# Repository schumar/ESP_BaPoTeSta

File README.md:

#  ESP8266 Battery Powered Temperature Station

## Moved to GitLab

This project has moved to [GitLab/schumar/ESP_BaPoTeSta](https://gitlab.com/schumar/ESP_BaPoTeSta)

## Intro

Using only an ESP8266 (no Atmel AVR) and a sensor, it's possible to build a very cheap and power-efficient WiFi-enabled weather station.

### Pictures of v0.3

### Pictures of v0.5

### Pictures of v0.6

### Maintenance Web-Interface

## Current state

I've already built 3 sensors of v0.3, and around 60 of v0.5.  
Right now I'm working on a major redesign of the board, and improving the firmware.

The sensors are reporting their data via MQTT, so the data can be received with [OpenHAB](http://www.openhab.org/),
[FHEM](http://fhem.de/fhem.html) or a small Perl script.

"Release early, release often" -- so don't expect to be able to clone this repo and have a working IoThingy 10 minutes later :)

## Screenshot

## Technical details

-> Read the source, stare at my KiCAD schematic :)

## BOM

Quick calculation: 1 board would cost ca. 4.81 to 7.50 USD (excl. batteries),
depending on which sensors you want. (Calculation for an order of 30 boards)

Part|Need/Board|URL|per piece|per board
----|---------:|---|----------:|----------:|
PCB|1|http://dev.dangerousprototypes.com/store/pcbs|0.50|0.50
PinHdr|11|http://www.aliexpress.com/item/x/32537378399.html|0.01|0.09
1uF 1206|2|http://www.aliexpress.com/store/1361740|0.03|0.06
10uF|1|http://www.aliexpress.com/item/x/32260294384.html|0.07|0.07
ESP8266|1|http://www.aliexpress.com/item/x/32519328481.html|1.93|1.93
10k 1206|10|http://www.aliexpress.com/item/x/32569352008.html|0.01|0.09
56k 1206|1|http://www.aliexpress.com/item/x/32567865953.html|0.02|0.02
MCP1700|1|http://www.aliexpress.com/item/x/32523953207.html|0.36|0.36
BatteryCase|1|http://www.aliexpress.com/item/x/2022527017.html|1.06|1.06
**Sub-Total**||||**4.18**
DS18B20|1|http://www.aliexpress.com/item/x/32576213069.html|0.63|0.63
DHT22|1|http://www.aliexpress.com/item/x/32544057083.html|2.70|2.70
**Only DS18B20**||||**4.81**
**Only DHT22**||||**6.87**
**Both**||||**7.50**

## To Do

see [Issues](https://gitlab.com/schumar/ESP_BaPoTeSta/issues)

## Thanks

* Many thanks to all the people working on the [Arduino core for ESP8266](https://github.com/esp8266/Arduino)
* Cheers to [jdunmire](https://github.com/jdunmire/kicad-ESP8266) for his ESP8266 KiCAD library!

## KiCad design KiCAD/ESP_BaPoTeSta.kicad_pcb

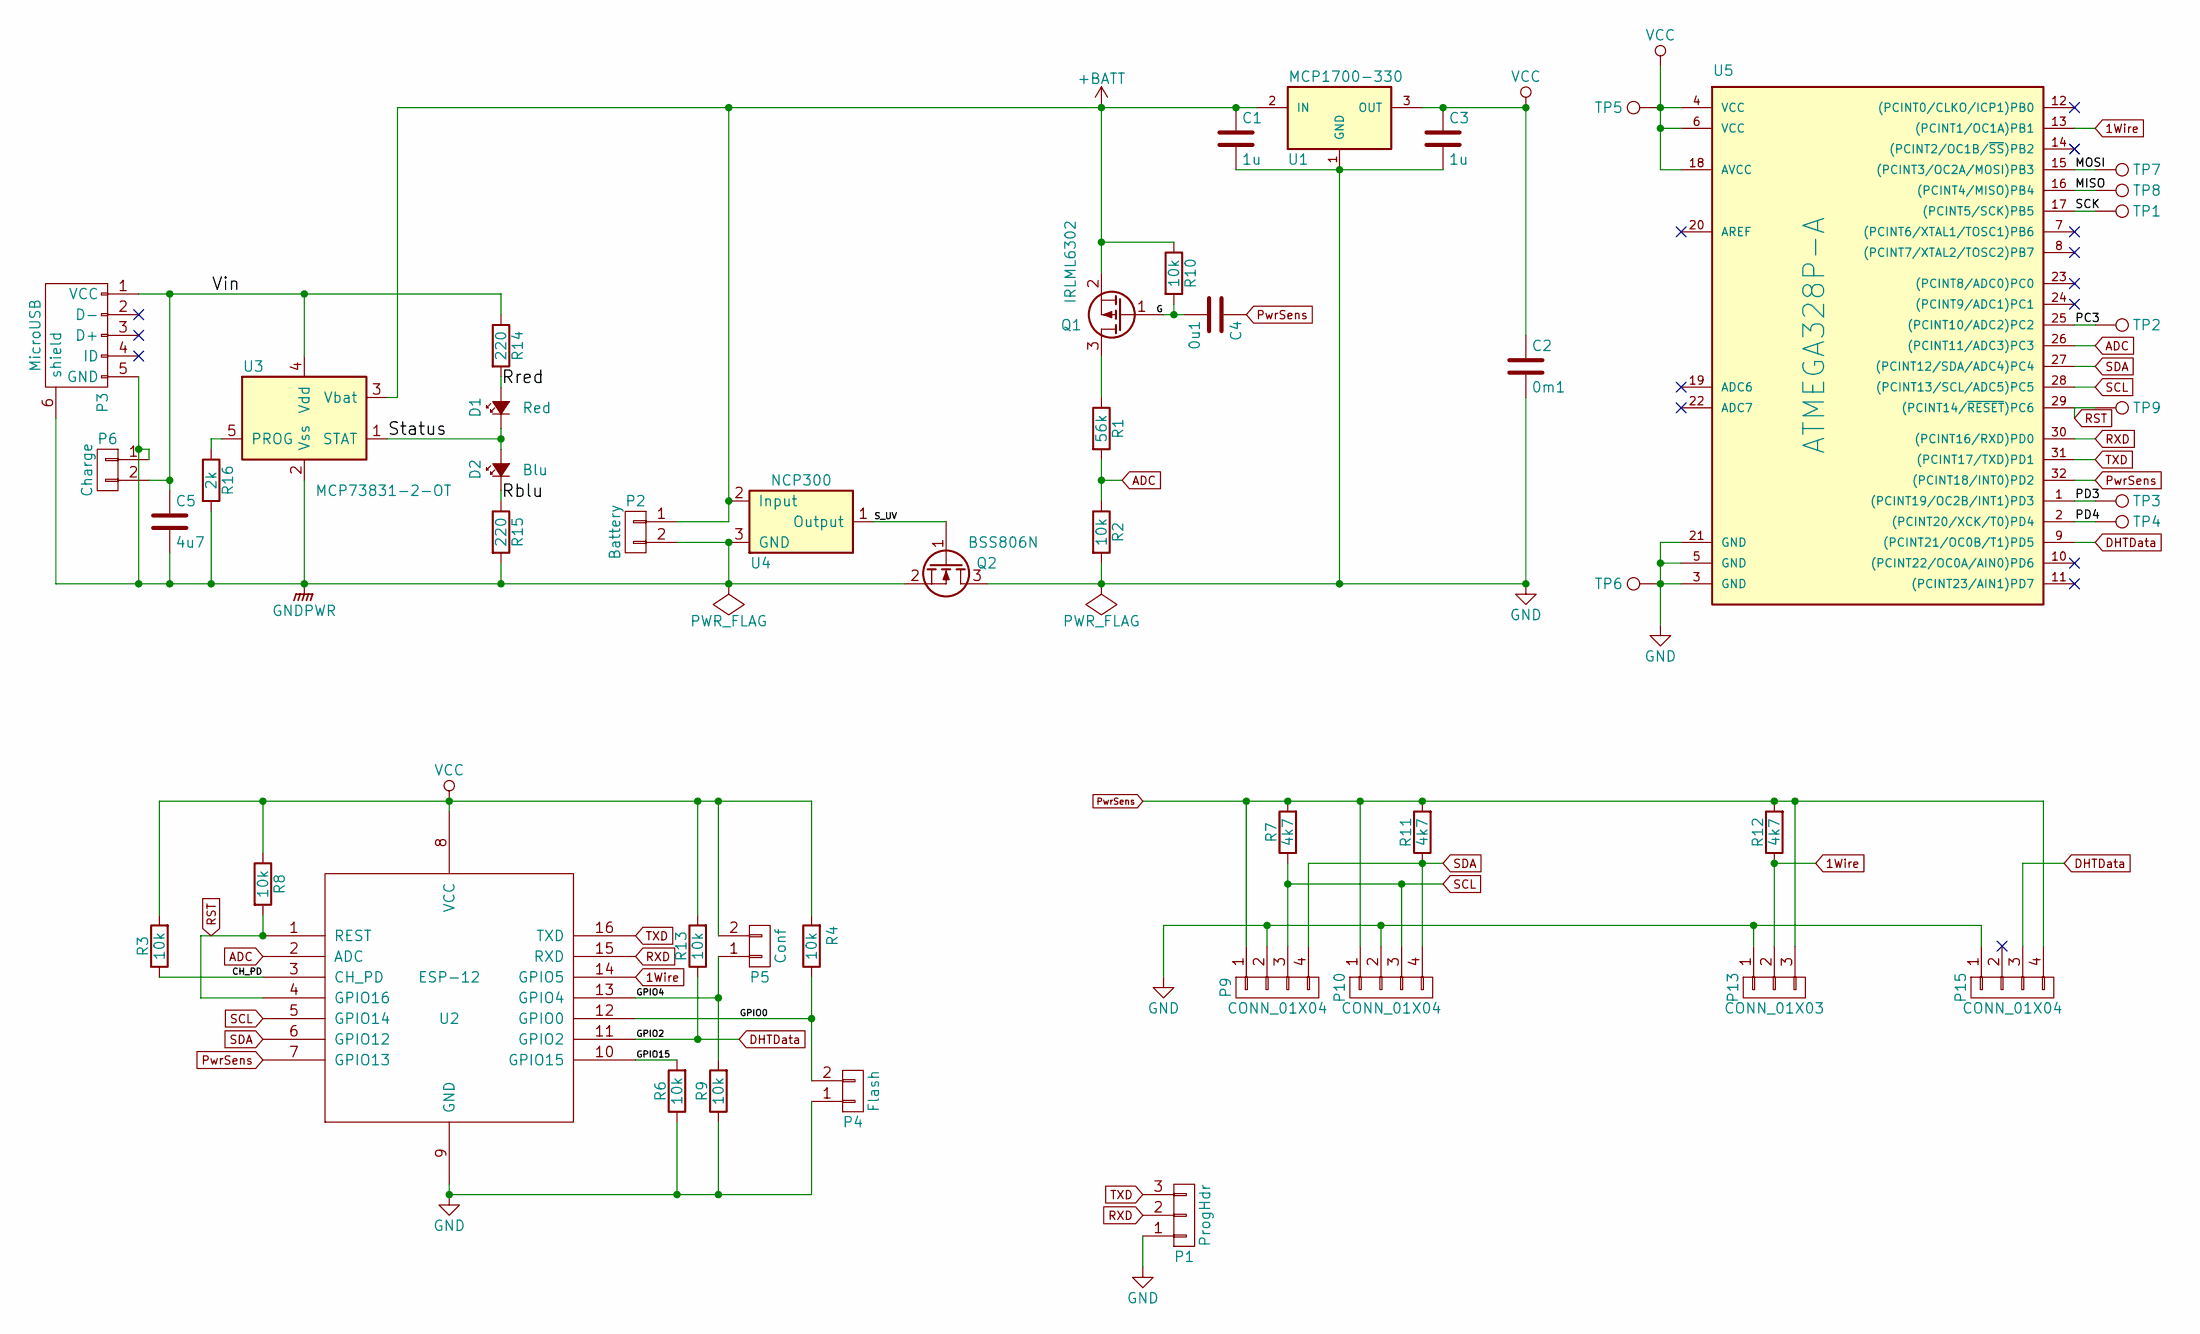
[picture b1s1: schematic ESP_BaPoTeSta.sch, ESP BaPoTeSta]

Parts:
C1, C3: 1u; C_1206_HandSoldering
C2: 0m1; C_1206_HandSoldering
C4: 0u1; C_1206_HandSoldering
C5: 4u7; C_1206_HandSoldering
D1: Red; LED_0805
D2: Blu; LED_0805
P1: ProgHdr; Pin_Header_Straight_1x03
P2: Battery; Pin_Header_Straight_1x02
P3: MicroUSB; USB_Micro-B
P4: Flash; Pin_Header_Straight_1x02
P5: Conf; Pin_Header_Straight_1x02
P6: Charge; Pin_Header_Straight_1x02
P9, P10, P15: CONN_01X04; Socket_Strip_Straight_1x04
P13: CONN_01X03; Socket_Strip_Straight_1x03
Q1: IRLML6302; SOT-23_Handsoldering
Q2: BSS806N; SOT-23_Handsoldering
R1: 56k; R_1206_HandSoldering
R2, R3, R4, R6, R8, R9, R10, R13: 10k; R_1206_HandSoldering
R7, R11, R12: 4k7; R_1206_HandSoldering
R14, R15: 220; R_1206_HandSoldering
R16: 2k; R_1206_HandSoldering
TP1, TP2, TP3, TP4, TP5, TP6, TP7, TP9: TEST_1P; Measurement_Point_Square-SMD-Pad_Small
TP8: TEST_1P; Measurement_Point_Round-SMD-Pad_Small
U1: MCP1700-330; SOT-23_Handsoldering
U2: ESP-12
U3: MCP73831-2-OT; SOT-23-5
U4: NCP300; SOT-23-5
U5: ATMEGA328P-A; TQFP-32_7x7mm_Pitch0.8mm

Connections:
1Wire: P13.2, R12.1, U2.14 (GPIO5), U5.13 ((PCINT1/OC1A)PB1)
+BATT: C1.1, P2.1, Q1.2 (S), R10.1, U1.2 (IN), U3.3 (Vbat), U4.2 (Input)
/CH_PD: R3.1, U2.3 (CH_PD)
/G: C4.2, Q1.1 (G), R10.2
/GPIO0: P4.2, R4.1, U2.12 (GPIO0)
/GPIO4: P5.1, R9.2, U2.13 (GPIO4)
/GPIO15: R6.2, U2.10 (GPIO15)
/MISO: TP8.1, U5.16 ((PCINT4/MISO)PB4)
/MOSI: TP7.1, U5.15 ((PCINT3/OC2A/MOSI)PB3)
/PC3: TP2.1, U5.25 ((PCINT10/ADC2)PC2)
/PD3: TP3.1, U5.1 ((PCINT19/OC2B/INT1)PD3)
/PD4: TP4.1, U5.2 ((PCINT20/XCK/T0)PD4)
/Rblu: D2.1 (K), R15.1
/Rred: D1.2 (A), R14.2
/SCK: TP1.1, U5.17 ((PCINT5/SCK)PB5)
/S_UV: Q2.1 (G), U4.1 (Output)
/Status: D1.1 (K), D2.2 (A), U3.1 (STAT)
/Vin: C5.1, P3.1 (VCC), P6.2, R14.1, U3.4 (Vdd)
ADC: R1.2, R2.1, U2.2 (ADC), U5.26 ((PCINT11/ADC3)PC3)
DHTData: P15.3, R13.1, U2.11 (GPIO2), U5.9 ((PCINT21/OC0B/T1)PD5)
GND: C1.2, C2.2, C3.2, P1.1, P4.1, P9.2, P10.2, P13.1, P15.1, Q2.3 (D), R2.2, R6.1, R9.1, TP6.1, U1.1 (GND), U2.9 (GND), U5.3 (GND), U5.5 (GND), U5.21 (GND)
GNDPWR: C5.2, P2.2, P3.5 (GND), P3.6 (shield), P6.1, Q2.2 (S), R15.2, R16.2, U3.2 (Vss), U4.3 (GND)
unnamed: Q1.3 (D), R1.1
unnamed: R16.1, U3.5 (PROG)
PwrSens: C4.1, P9.1, P10.1, P13.3, P15.4, R7.2, R11.2, R12.2, U2.7 (GPIO13), U5.32 ((PCINT18/INT0)PD2)
RST: R8.2, TP9.1, U2.1 (REST), U2.4 (GPIO16), U5.29 ((PCINT14/~RESET~)PC6)
RXD: P1.2, U2.15 (RXD), U5.30 ((PCINT16/RXD)PD0)
SCL: P9.3, P10.3, R7.1, U2.5 (GPIO14), U5.28 ((PCINT13/SCL/ADC5)PC5)
SDA: P9.4, P10.4, R11.1, U2.6 (GPIO12), U5.27 ((PCINT12/SDA/ADC4)PC4)
TXD: P1.3, U2.16 (TXD), U5.31 ((PCINT17/TXD)PD1)
VCC: C2.1, C3.1, P5.2, R3.2, R4.2, R8.1, R13.2, TP5.1, U1.3 (OUT), U2.8 (VCC), U5.4 (VCC), U5.6 (VCC), U5.18 (AVCC)

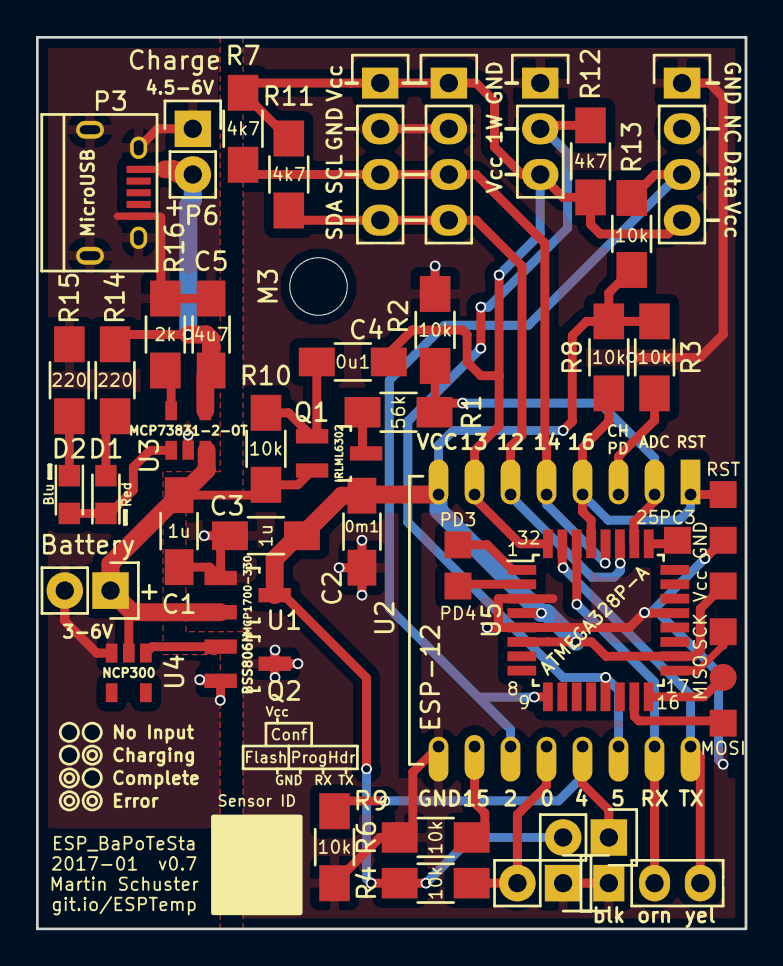
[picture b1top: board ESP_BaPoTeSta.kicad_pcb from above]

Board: 2 copper layers, 39.4 x 49.5 mm, 49 parts (0 on the bottom side), 31 nets.

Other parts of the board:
M3: MountingHole_3.2mm_M3_ISO7380

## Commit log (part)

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2015-11-06 GIT: initial checkin
2015-11-06 GIT: Rename project
2015-11-06 SRC: indentation (4 instead of 2)
2015-11-06 SRC: we don't use the blue LED
    so don't call it blue LED :)
2015-11-06 ENH: power PTC only when needed
2015-11-06 BUG: SLEEPSEC was off by factor 10
2015-11-06 SRC: more todo-items
2015-11-06 ENH: check for WiFi status instead of blindly waiting
2015-11-06 SRC: clarify "timestamp" todo-item
2015-11-06 ENH: allow connections to password-protected WLAN
2015-11-06 ENH: Send packet twice
    UDP gets lost sometimes
2015-11-06 ENH: calculate temperature
    instead of just sending ADC-values
2015-11-25 SRC: add some more cool ideas
    CoAP, timestamp
2015-11-26 ENH: faster check for WiFi connection
2015-11-26 CFG: specified wrong Rfix
2015-11-26 ENH: Correctly calculate temperature
    Formula: https://en.wikipedia.org/wiki/Thermistor#B_or_.CE.B2_parameter_equation
    Values for my thermistor (MF52-103/3950) taken from datasheet
    (doubled R0, as I'm using 2 of those in series)
2015-11-26 CFG: simple fix for inaccurate measurements
    dunno why my ADC reports too /big/ values instead of too low.
    But tested with multimeter: 0.645V got reported as "670", 670/1024 = 0.655
2015-11-26 TXT: My thermistor is an NTC, not PTC
    fix variable names and comments
2015-11-28 ENH: wait between and after sending packets
    to make sure they get sent before we go to deep_sleep
2015-11-28 ENH: don't send chipId
    KISS. we can just use the source IP if necessary
    to distinguish multiple sensors
2015-11-29 BUG: switch off blue LED for no-WiFi-sleep
    move "switch off blue LED + deepSleep" to dedicated function
2015-11-29 ENH: Send decimal temp value
    rewrite of the part building the packetBuffer
2015-11-29 CFG: only sleep for 299s instead of 300s
    as booting + data acquisition needs ca. 1.2s
2015-11-29 CFG: sleep a little longer
    looks like the timer isn't very accurate, mine sleeps 291s instead of 299s
2015-12-05 GIT: ignore more KiCad files
2015-12-05 GIT: add README
2015-12-05 GIT: add LICENSE (GNU GPL 3)
2015-12-05 TXT: moved "TODO" stuff to github Issues
2015-12-05 TXT: Thank jdunmire
2015-12-05 TXT: add nice picture of board to README
2015-12-05 TXT: add newline to "Intro"
2015-12-06 TXT: fine-tune silk-screen
    move labels, put most "Values" in F.SilkS, add some pin labels.
    fixes #5, fixes #8
2015-12-06 TXT: fix orientation of front-side label
    so it's the same direction as all other labels
2015-12-06 TXT: add voltage range to battery header
2015-12-06 ENH: Make board more compact
    by moving the battery header. Now only 40x50mm (was 50x50mm)
2015-12-06 TXT: add BOM
    fixes #8
2015-12-07 TXT: add silk-screen rect for Sensor ID
    so I can write some number on each sensor board
2015-12-07 ENH: add Power header
    might be useful
2015-12-07 ENH: consistently use rectangular pads for GND
2015-12-07 TXT: use cheaper battery box for BOM
    now we are down to 6$/board
2015-12-07 ENH: Move buttons closer to the edge of the PCB
2015-12-08 TXT: update image with current version of board
    this is what my order at dirtypcbs might look like
2015-12-10 SRC: move config to extra file
2015-12-10 SRC: rename MEASURES to NTC_MEASURES
    and make bubbleSort independent of that const
2015-12-12 ENH: add config option if NTC should be used
2015-12-12 ENH: also send raw NTC data
2015-12-12 ENH: add support for Dallas temp-sensors
    see #1
2015-12-12 BUG: 1Wire-pin was hardcoded and wrong
    see #12
2015-12-12 SRC: rename calcTemp to calcNTCTemp
    just to make it clear that this is NTC-specific
2015-12-12 CFG: use another port
    Now that our "protocol" has changed, also change the port,
    so we don't accidentally feed JSON to the old parser (or the
    other way round)
2015-12-12 SRC: Move reading of ADC to extra function
    preparation for reading battery voltage, see #9
2015-12-13 BUG: fix invalid JSON
    forgot to increase pointer. I hate C.
2015-12-13 BUG: measurements need to end up as integer
    so we can easily put them into JSON
    (Arduino sprintf can't do %f)
2015-12-13 ENH: support having an always-on Dallas sensor
    As the DS18B20 only needs 5uA according to the datasheet,
    having a dedicated pin to power it seems a waste of pins
2015-12-13 ENH: add legend for previous period to graphs
2015-12-13 ENH: add wunderground-data to week-graph too
2015-12-13 BUG: wrong formatting for values in legend
2015-12-13 ENH: put both temp sensors in graphs
    This code is getting uglier every minute.
    Should start redoing it in Perl
2016-01-01 ENH: Use MQTT
    instead of just UDP.
    untested
2016-01-01 SRC: add new sensorType "time"
    can be used to e.g. measure the time it takes to measure everything
2016-01-01 ENH: Measure measurement-time
2016-01-05 ENH: Start implementing DHT support
    see #1
2016-01-05 ENH: Only init dallas sensor if doDallas is true
2016-01-05 ENH: support DHT sensors
    fixes #13
2016-01-07 BUG: Forgot to measure battery voltage
2016-01-07 SRC: use "long" format for chipId-sprintf
    gcc complained (correctly)
2016-01-07 BUG: Forgot to actually measure DHT
2016-01-07 BUG: battery "divider" constant was 0
    need to do float division
2016-01-07 TXT: only send values via MQTT, no "value="
    much easier to parse on openHAB-side
2016-01-07 WIP: Continue improving PCB
    continue the work started in 0493dcc
    add additional header to enter config mode
2016-01-09 ENH: Improve PCB
    Finalize work started in 0493dcc and 57554c2
    Add DHT22 (you can now install 2 sensors, DHT22 and DS18B20)
    Fix the various bugs (fixes #14, fixes #15, fixes #16)
    Avoid ground-fill at DS18B20 GND pin (improves accuracy)
    Drop the 2 push-buttons
    Board now much smaller (3x5cm)
2016-01-10 ENH: use small ceramic buffer caps
    lower ESR. Still use one additional big electrolytic cap
2016-01-10 ENH: [pcb] add strain relief for battery cable
    and change type of 3mm-mounting-hole from "1pin" to "MountingHole"
2016-01-10 ENH: improve battery measurement accuracy
    use 56k instead of 68k resistor
    This will work up to 6.6V -- more than enough, as max
    rated input voltage of the MCP1700 is only 6V
2016-01-10 TXT: [pcb] label ESP pin usage, etc
    label the 3 areas (Programming, PSU, Sensors)
    align ESP pin labels
    hide some "Fab" text
2016-01-11 ENH: make blue LED optional
2016-01-11 ENH: [pcb] add measurement point at GPIO4
    The only unused pin, can now be used for custom hacks
2016-01-12 TXT: add picture of finished v0.3 board
2016-01-12 GIT: missed a line at last merge 59a1d02
2016-01-12 TXT: add rendered picture of v0.5 board
2016-01-13 GIT: replace "server" parts
    receive data via MQTT, automatically create graphs out of
    all available RRD files, show them on a nice webpage
2016-01-13 TXT: add links to OpenHAB and FHEM
2016-01-14 ENH: [pcb] minor silkscreen fixes
    also, finish f41bc1a
2016-01-15 WIP: start work on "config mode"
    see #10
2016-01-16 TXT: add "Hacking" instructions
2016-01-16 ENH: Enable serial debugging
2016-01-16 ENH: Make webserver work
    Having the webserver stuff outside loop() triggers the watchdog
    Now everything is clean and working
    see #10
2016-01-17 WIP: move index-handler to dedicated function
    and use sprintf -- which seems to break everything :(
2016-01-17 TXT: Use double quotes in HTML
2016-01-17 BUG: forgot a "<" in HTML
2016-01-17 WIP: start work on config-in-eeprom
2016-01-18 SRC: fill config structure
    and add defaults
2016-01-18 ENH: Complete web form
2016-01-18 BUG: DS18B20 resolution is 9..12, not 10..13
2016-01-24 WIP: use 5 more params from config struct
2016-01-24 SRC: remove unused "sleepUDP" config
2016-01-24 ENH: NTC now also configurable
2016-01-27 BUG: need to prototype storeConfig()
2016-01-27 WIP: Convert received parameters to config struct
    still need to actually store it!
2016-01-28 BUG: IP parsing error
    accidentally increased i twice
2016-01-28 DBG: add debug print for "found 0x42"
    so we know that the EEPROM contains config
2016-01-29 DOC: add screenshot of webinterface
2016-02-01 DOC: fix markdown-syntax
    github wants "###" header marks.
2016-02-01 DOC: Test board by switching it on
2016-02-04 STY: typo in comment
2016-02-04 ENH: more debugPrint()s
    for WiFi and form-POST
2016-02-04 ENH: Save RAM by moving CSS to flash
2016-02-04 ENH: even more debugPrint()s
2016-02-04 CFG: disable SERIALDEBUG
    this shouldn't be enabled by default
2016-03-26 SRC: add newlines for readability
2016-04-19 add zabbix template
2016-04-20 ENH: sanity check temp/humidity values
    compare measured values with possible range of the sensors
    fixes #28
2016-05-08 ENH: don't measure/send if Vbatt too low
    to avoid bogus data
2016-06-10 change URL for esp82 arduino IDE package
2016-06-13 ENH: Redesigned schematic
    now with 4 I2C, 2 1Wire and 1 DHT port.
    Also added MOSFET for battery measurement,
    and power-saving Schottky for GPIO16 -- thanks Malte!
2016-06-21 WIP: continue work on new board
    remove diode, more/better labels,...
2016-06-21 BUG: Don't send "2147483647"
    The DHT lib returns NaN when sth went wrong; this didn't get
    caught by the comparison, so now check using isnan()
    see #28
2016-06-21 BUG: don't call dhtSensor.begin() when usedht is false
    looks like my brain was in Python-mode...
2016-06-21 ENH: Initial support for BMP280
2016-06-21 ENH: calculate pressure at sea level
2016-11-08 GIT: add kicad-ESP8266 as submodule
2016-11-08 SRC: PCB: cleanup KiCAD library paths
    not using open-project parts anymore
    use kicad-ESP8266 from the submodule
2016-11-08 SRC: PCB: reorder some stuff
    KiCAD has decided to change the order of those elements
2016-11-08 DOC: update status
    v0.5 has been built ages ago :)
2016-11-08 DOC: Manual: Remove rambling about South/East
    too confusing, and unnecessary
2016-11-08 ENH: PCB: add mounting holes
2016-11-08 TXT: PCB: some more cosmetics
    move labels around a bit
2016-11-09 ENH: PCB: minor cosmetical changes
    move left mounting hole
    move el.cap
    lines for pin labels at headers
2016-11-09 WIP: PCB: continued routing
2016-11-14 GIT: PCB: add kicad lib for mcp73831
2016-11-29 DOC: PCB: silkscreen improvements
    Fix size/position of labels
    swap GPIO 4<->5 labels
    add header diagram
    fix voltage labels (ESP needs 2.5V in, so 3.0V battery is ok)
2016-11-30 GIT: remove net-file
    This will be generated by KiCAD anyway, no use in commiting
    every little change
2016-12-03 ENH: PCB: add NCP300 component
    My first KiCAD component :)
    see #36
2016-12-03 ENH: CFG: Increase sleep time on low battery voltage
    Another minor measure to prevent deep discharge of the battery
2016-12-03 DOC: SCH: Improve schematic layout
    Join battery charger and voltage regulation parts
    Move parts around
    Fix Rev/Date
2016-12-04 ENH: PCB: Most traces are now 0.5mm
    0.5mm (20mill) are more than enough for the low currents (500mA)
    Only the "main" trace (USB+ to MCP73831 to battery to MCP1700 to ESP)
    is still 1mm (40mill).
    GND is transferred via the copper planes.
    fixes #31
2016-12-04 WIP: PCB: Route ATmega
    and add some test points
2016-12-04 ENH: PCB: Make it easier to attach a 433 sender
    Add solder pads for GND and SMD, and move the pads for PB5 and PC1 to
    the border of the board
    see #34
2016-12-04 ENH: PCB: add charging connector
2016-12-05 GIT: ignore BOM output
2016-12-05 ENH: PCB: Minor cosmetic fixes
    remove a remaining "no_connect" (between 2 GND pins of ATmega)
    hide "TEST_1P" labels
    remove "blk" label which was below a pin header
    remove some useless traces
2016-12-06 DOC: add render of v0.6 with ATmega
    see #34
2016-12-10 SRC: [fw] Drop NTC support
    Not usable since board v0.5
2017-01-05 ENH: pcb: minor cosmetic enhancements
    remove rectangle in SOT23-5 parts
    replace tiny LED symbol with cathode-marker for 1206 LEDs
    remove tiny "TPx" labels
    move some labels
    label C2 as "0m1" instead of "100u" so it's readable on PCB
    make "LED off" symbols darker by removing copper fill
2017-01-05 ENH: PCB: improve PD3/PD4 pads
    align on 100mill raster, add a GND pad
2017-02-19 ENH: fw: send WiFi strength
    fixes #42
2017-02-26 BUG: [fw] Workaround for #43
    Pull PwrSens LOW right before measuring the battery voltage
    On my prototype, replaced C4 (0.1uF) with 4.7uF, which allows for
    ~50ms of measuring; set sleepADCmeasure to 2(ms), so we are done in
    ~10ms.
    The source looks a bit ugly now, need to rethink this; definitely when
    using the AVR, as setup() won't be called at each run anymore
2017-02-26 TXT: [fw] typo in comment
